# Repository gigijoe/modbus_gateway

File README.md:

## ESP32 Modbus TCP / RTU / ASCII Gateway

#### Hardware
ESP32 TTGO T8V1.7 16MB FLASH / 8MB PSRAM

#### Feature
1.Combine Modbus TCP slave and Modbus RTU / ASCII master to act as Modbus TCP / RTU / ASCII Gateway\
2.Supports maximum 8 Modbus TCP connections synchronously. Listen on port 503\
3.Supports Modbus TCP slave of 8 digital input and 8 digital output locally. Listen on port 502\
4.Supports Wifi Access Point / Station / Ethernet network\
5.Supports mDNS service for zero IP configuration\
6.Supports DS1307 hardware RTC\
7.Supports NTP client\
8.Supports 1 port DS18B20 temperature sensor\
9.Supports 1 port ADC voltage reading\
10.Supports 20 x 4 dot matric LCD\

#### Reference

https://github.com/maxx-ukoo/esp32-modbus-tcp2rtu

https://github.com/iot-lorawan/esp32-ota-ble

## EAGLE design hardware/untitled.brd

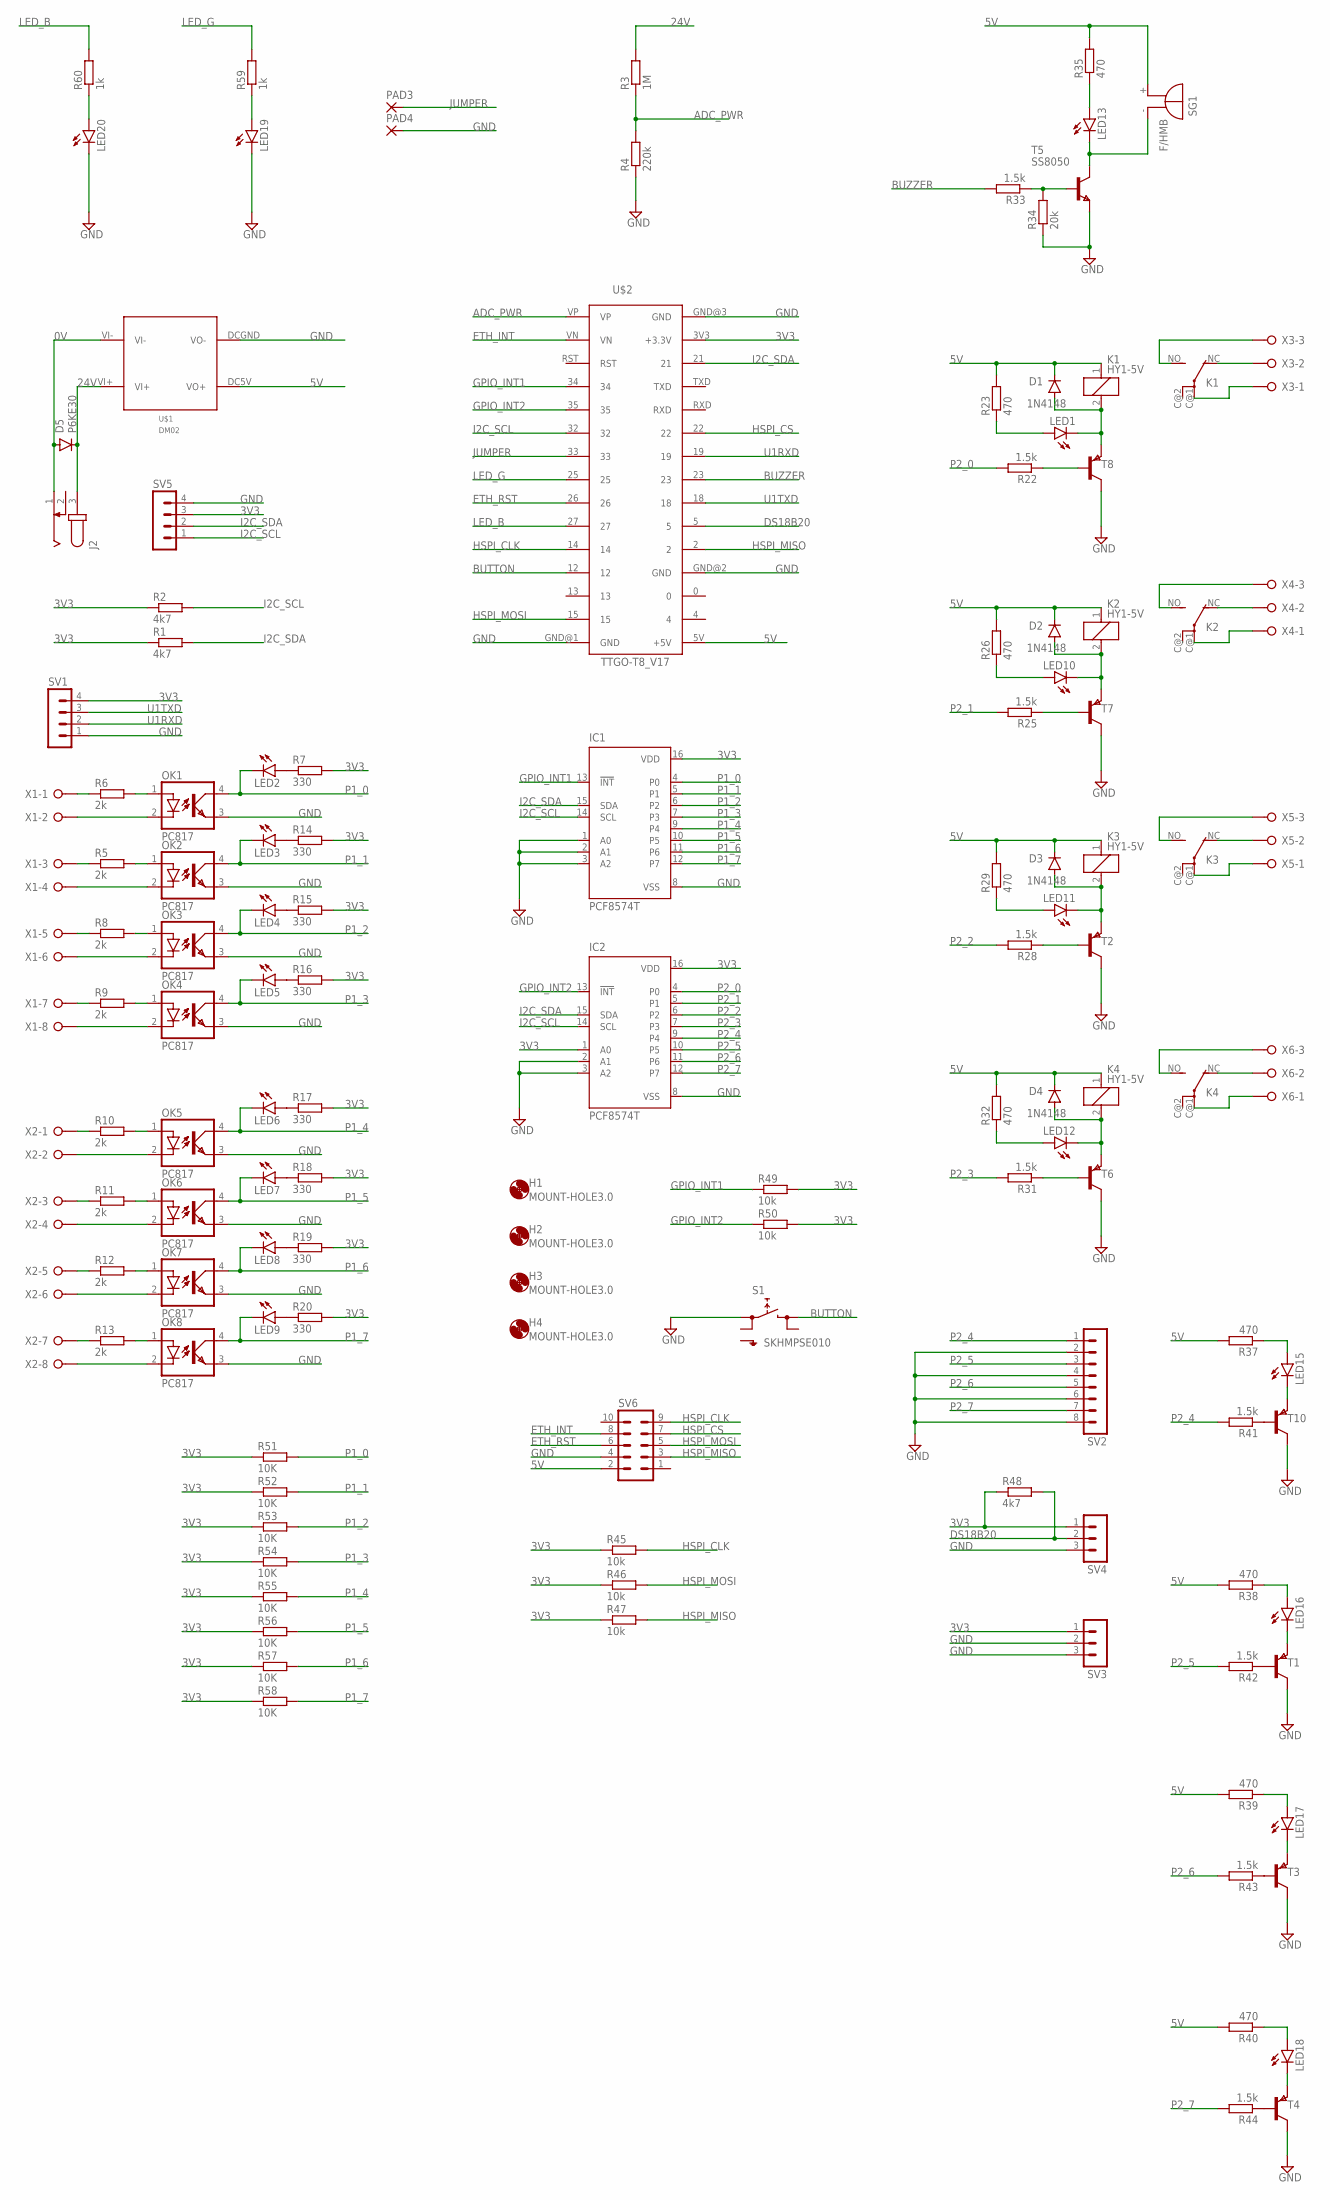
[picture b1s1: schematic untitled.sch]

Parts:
D1, D2, D3, D4: 1N4148; SOD123
D5: P6KE30; D-10
H1, H2, H3, H4: MOUNT-HOLE3.0; 3,0
IC1, IC2: PCF8574T; SO16W
J2: JACK-PLUG0; SPC4077
K1, K2, K3, K4: HY1-5V; HY
LED1, LED2, LED3, LED4, LED5, LED6, LED7, LED8, LED9, LED10, LED11, LED12, LED13, LED15, LED16, LED17, LED18, LED19, LED20: LEDCHIPLED_0805; CHIPLED_0805
OK1, OK2, OK3, OK4, OK5, OK6, OK7, OK8: PC817; DIL04
PAD3, PAD4: 2,15/1,0
R1, R2, R48: 4k7; R0603
R3: 1M; R0603
R4: 220k; R0603
R5, R6, R8, R9, R10, R11, R12, R13: 2k; R0603
R7, R14, R15, R16, R17, R18, R19, R20: 330; R0603
R22, R25, R28, R31, R33, R41, R42, R43, R44: 1.5k; R0603
R23, R26, R29, R32, R35, R37, R38, R39, R40: 470; R0603
R34: 20k; R0603
R45, R46, R47, R49, R50: 10k; R0603
R51, R52, R53, R54, R55, R56, R57, R58: 10K; R0603
R59, R60: 1k; R0603
S1: SKHMPSE010; SKHMPXE010
SG1: F/HMB
SV1, SV5: MA04-1
SV2: MA08-1
SV3, SV4: MA03-1
SV6: MA05-2
T1, T2, T3, T4, T6, T7, T8, T10: PNPSOT23; SOT-23
T5: SS8050; SOT-23
U$1: DM02
U$2: TTGO-T8_V17
X1, X2: W237-08P; W237-8P
X3, X4, X5, X6: W237-03P; W237-133

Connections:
0V: D5.A, J2.1, U$1.VI-
3V3: IC1.16 (VDD), IC2.1 (A0), IC2.16 (VDD), R1.1, R2.1, R7.2, R14.2, R15.2, R16.2, R17.2, R18.2, R19.2, R20.2, R45.1, R46.1, R47.1, R48.1, R49.2, R50.2, R51.1, R52.1, R53.1, R54.1, R55.1, R56.1, R57.1, R58.1, SV1.4, SV3.1, SV4.1, SV5.3, U$2.3V3 (+3.3V)
5V: D1.C, D2.C, D3.C, D4.C, K1.1, K2.1, K3.1, K4.1, R23.2, R26.2, R29.2, R32.2, R35.2, R37.2, R38.2, R39.2, R40.2, SG1.+, SV6.2, U$1.DC5V (VO+), U$2.5V (+5V)
24V: D5.C, J2.3, R3.2, U$1.VI+
ADC_PWR: R3.1, R4.2, U$2.VP
BUTTON: S1.3 (2.1), U$2.12
BUZZER: R33.2, U$2.23
DS18B20: R48.2, SV4.2, U$2.5
ETH_INT: SV6.8, U$2.VN
ETH_RST: SV6.6, U$2.26
GND: IC1.1 (A0), IC1.2 (A1), IC1.3 (A2), IC1.8 (VSS), IC2.2 (A1), IC2.3 (A2), IC2.8 (VSS), LED19.C, LED20.C, OK1.3 (EMIT), OK2.3 (EMIT), OK3.3 (EMIT), OK4.3 (EMIT), OK5.3 (EMIT), OK6.3 (EMIT), OK7.3 (EMIT), OK8.3 (EMIT), PAD4.1, R4.1, R34.1, S1.1 (1.1), SV1.1, SV2.2, SV2.4, SV2.6, SV2.8, SV3.2, SV3.3, SV4.3, SV5.4, SV6.4, T1.1 (C), T2.1 (C), T3.1 (C), T4.1 (C), T5.2 (E), T6.1 (C), T7.1 (C), T8.1 (C), T10.1 (C), U$1.DCGND (VO-), U$2.GND@1 (GND), U$2.GND@2 (GND), U$2.GND@3 (GND)
GPIO_INT1: IC1.13 (!INT), R49.1, U$2.34
GPIO_INT2: IC2.13 (!INT), R50.1, U$2.35
HSPI_CLK: R45.2, SV6.9, U$2.14
HSPI_CS: SV6.7, U$2.22
HSPI_MISO: R47.2, SV6.3, U$2.2
HSPI_MOSI: R46.2, SV6.5, U$2.15
I2C_SCL: IC1.14 (SCL), IC2.14 (SCL), R2.2, SV5.1, U$2.32
I2C_SDA: IC1.15 (SDA), IC2.15 (SDA), R1.2, SV5.2, U$2.21
JUMPER: PAD3.1, U$2.33
LED_B: R60.2, U$2.27
LED_G: R59.2, U$2.25
unnamed: R5.1, X1.3
unnamed: R6.1, X1.1
unnamed: OK1.1 (A), R6.2
unnamed: OK1.2 (C), X1.2
unnamed: OK2.1 (A), R5.2
unnamed: OK2.2 (C), X1.4
unnamed: R8.1, X1.5
unnamed: OK3.1 (A), R8.2
unnamed: OK3.2 (C), X1.6
unnamed: R9.1, X1.7
unnamed: OK4.1 (A), R9.2
unnamed: OK4.2 (C), X1.8
unnamed: R10.1, X2.1
unnamed: OK5.1 (A), R10.2
unnamed: OK5.2 (C), X2.2
unnamed: R11.1, X2.3
unnamed: OK6.1 (A), R11.2
unnamed: OK6.2 (C), X2.4
unnamed: R12.1, X2.5
unnamed: OK7.1 (A), R12.2
unnamed: OK7.2 (C), X2.6
unnamed: R13.1, X2.7
unnamed: OK8.1 (A), R13.2
unnamed: OK8.2 (C), X2.8
unnamed: R25.1, T7.3 (B)
unnamed: LED1.A, R23.1
unnamed: D2.A, K2.2, LED10.C, T7.2 (E)
unnamed: LED2.A, R7.1
unnamed: LED3.A, R14.1
unnamed: LED4.A, R15.1
unnamed: LED15.A, R37.1
unnamed: LED16.C, T1.2 (E)
unnamed: LED5.A, R16.1
unnamed: LED19.A, R59.1
unnamed: R22.1, T8.3 (B)
unnamed: D1.A, K1.2, LED1.C, T8.2 (E)
unnamed: K1.NO (S), X3.3
unnamed: K1.NC (O), X3.2
unnamed: R28.1, T2.3 (B)
unnamed: D3.A, K3.2, LED11.C, T2.2 (E)
unnamed: LED10.A, R26.1
unnamed: LED11.A, R29.1
unnamed: R31.1, T6.3 (B)
unnamed: D4.A, K4.2, LED12.C, T6.2 (E)
unnamed: LED12.A, R32.1
unnamed: K1.C@1, X3.1
unnamed: K2.NO (S), X4.3
unnamed: K2.NC (O), X4.2
unnamed: K2.C@1, X4.1
unnamed: K3.NO (S), X5.3
unnamed: K3.NC (O), X5.2
unnamed: K3.C@1, X5.1
unnamed: K4.NO (S), X6.3
unnamed: K4.NC (O), X6.2
unnamed: K4.C@1, X6.1
unnamed: LED15.C, T10.2 (E)
unnamed: LED20.A, R60.1
unnamed: R33.1, R34.2, T5.3 (B)
unnamed: R41.1, T10.3 (B)
unnamed: LED13.A, R35.1
unnamed: LED13.C, SG1.-, T5.1 (C)
unnamed: LED9.A, R20.1
unnamed: LED16.A, R38.1
unnamed: LED17.C, T3.2 (E)
unnamed: LED17.A, R39.1
unnamed: LED18.C, T4.2 (E)
unnamed: LED18.A, R40.1
unnamed: R42.1, T1.3 (B)
unnamed: R43.1, T3.3 (B)
unnamed: R44.1, T4.3 (B)
unnamed: LED8.A, R19.1
unnamed: LED7.A, R18.1
unnamed: LED6.A, R17.1
P1_0: IC1.4 (P0), LED2.C, OK1.4 (COL), R51.2
P1_1: IC1.5 (P1), LED3.C, OK2.4 (COL), R52.2
P1_2: IC1.6 (P2), LED4.C, OK3.4 (COL), R53.2
P1_3: IC1.7 (P3), LED5.C, OK4.4 (COL), R54.2
P1_4: IC1.9 (P4), LED6.C, OK5.4 (COL), R55.2
P1_5: IC1.10 (P5), LED7.C, OK6.4 (COL), R56.2
P1_6: IC1.11 (P6), LED8.C, OK7.4 (COL), R57.2
P1_7: IC1.12 (P7), LED9.C, OK8.4 (COL), R58.2
P2_0: IC2.4 (P0), R22.2
P2_1: IC2.5 (P1), R25.2
P2_2: IC2.6 (P2), R28.2
P2_3: IC2.7 (P3), R31.2
P2_4: IC2.9 (P4), R41.2, SV2.1
P2_5: IC2.10 (P5), R42.2, SV2.3
P2_6: IC2.11 (P6), R43.2, SV2.5
P2_7: IC2.12 (P7), R44.2, SV2.7
U1RXD: SV1.2, U$2.19
U1TXD: SV1.3, U$2.18

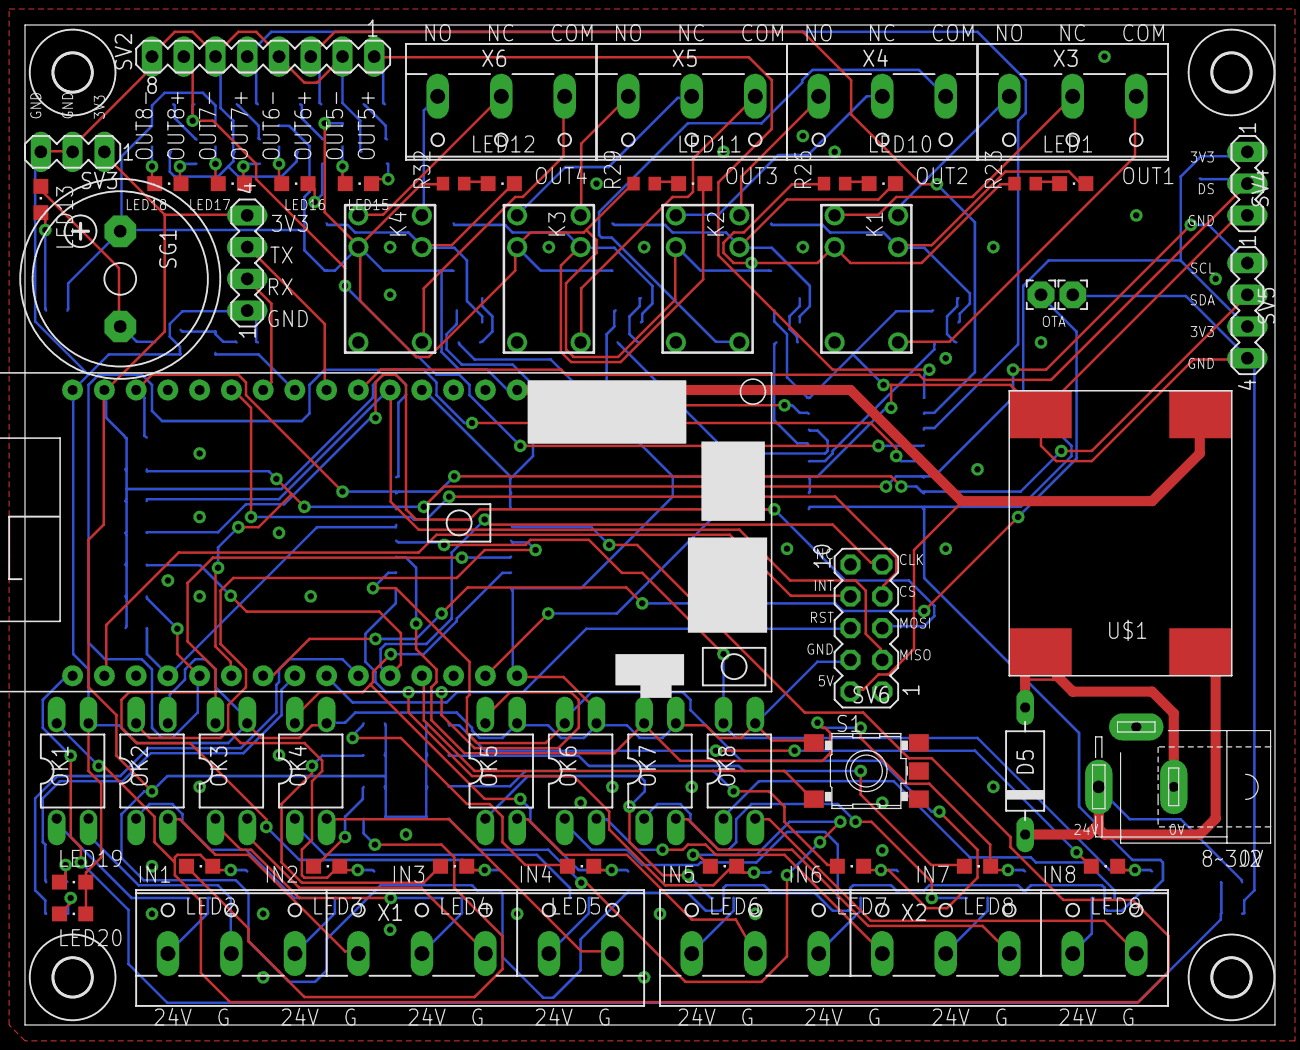
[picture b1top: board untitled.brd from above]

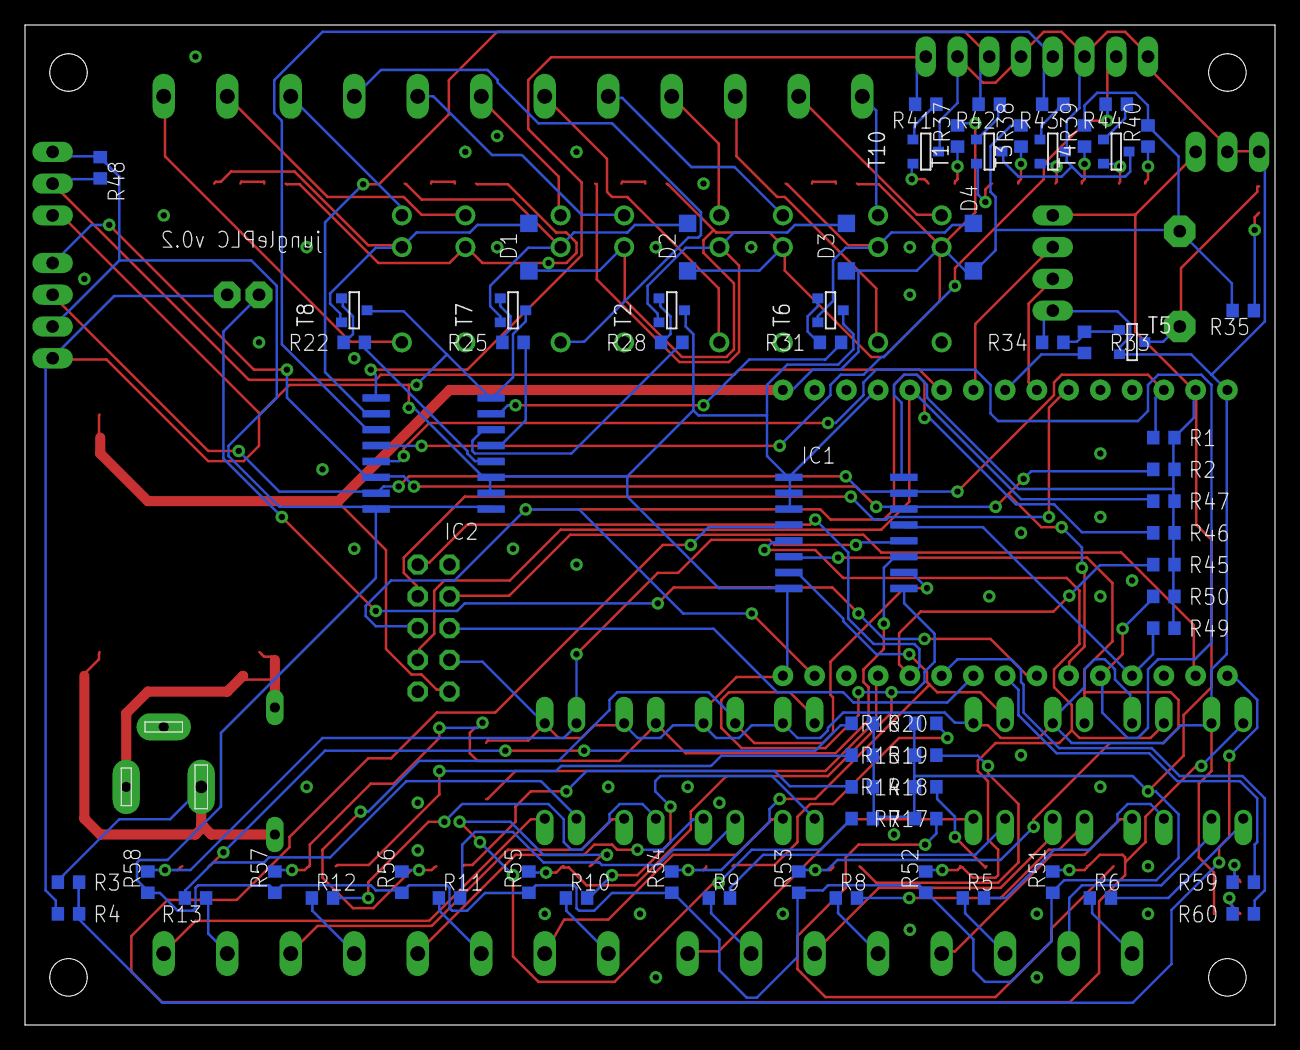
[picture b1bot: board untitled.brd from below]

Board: 2 copper layers, 100.0 x 80.0 mm, 125 parts (66 on the bottom side), 113 nets.

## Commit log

2021-12-24 Markdown new line
2022-01-13 1.New option of external digital input 2.Assign default netif to wifi AP when AP mode enable 3.Fix bug of wifi connected LED
2022-01-14 1.Support setting of AP channel 2.Varoius update of network
2022-01-14 1.Add wifi_scan_start 2.Fix project name
2022-01-18 1.Support sta channel, bssid / ap mac channel 2.Compatable for IDF 4.4.x 3.Support NAPT
2022-01-18 Fix bug of checking wifi get mac
2022-01-20 1.Support blufi 2.Various wifi / eth network bug fix
2022-01-21 1.Improve blufi coding struct 2.Add daisy chain config
2022-01-21 Set default AP IP to 172.16.0.1
2022-01-21 Fix bug of blufi set wifi sta password
2022-01-24 1.Add option of daisy chain network 2.Add option of blufi 3.More bug fix of network
2022-06-07 Various fix for esp-idf v5.0
